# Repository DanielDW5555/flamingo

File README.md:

# Flamingo

This is the first original project I have completed from start to finish. My inspiration for this project was flamingos, and how they are usually seen balanced upright on one leg. The goal of the project was to create a self balancing robot that could stand upright for a short period of time.

The system works by interfacing the LIS3LV02DLTR accelerometer with the STM32F3 microcontroller to monitor the x and z component of acceleration. The data from the accelerometer is then used by a PID control system implemented on the microcontroller which configures the PWM duty cycle of the brushed DC motors.

The following where the requirements I used to design the robot:
  - The robot must be able to stand up right during operation
  - The robot will be powered by a 9V battery
  - All electronic devices will be implemented on a single PCB
  - The size of the PCB will be equal to or smaller than a credit card
  - No price limit on the BOM (Although my wallet will regret this later...)

The assembled robot fulfills the requirements listed above, but the PID controller requires a lot of tuning to get it to stand upright. Having a larger robot would make tuning the PID control system easier.

The following images depict the blank flamingo PCB and the rev 1 schematic.

Blank PCB

Rev 1 schematic

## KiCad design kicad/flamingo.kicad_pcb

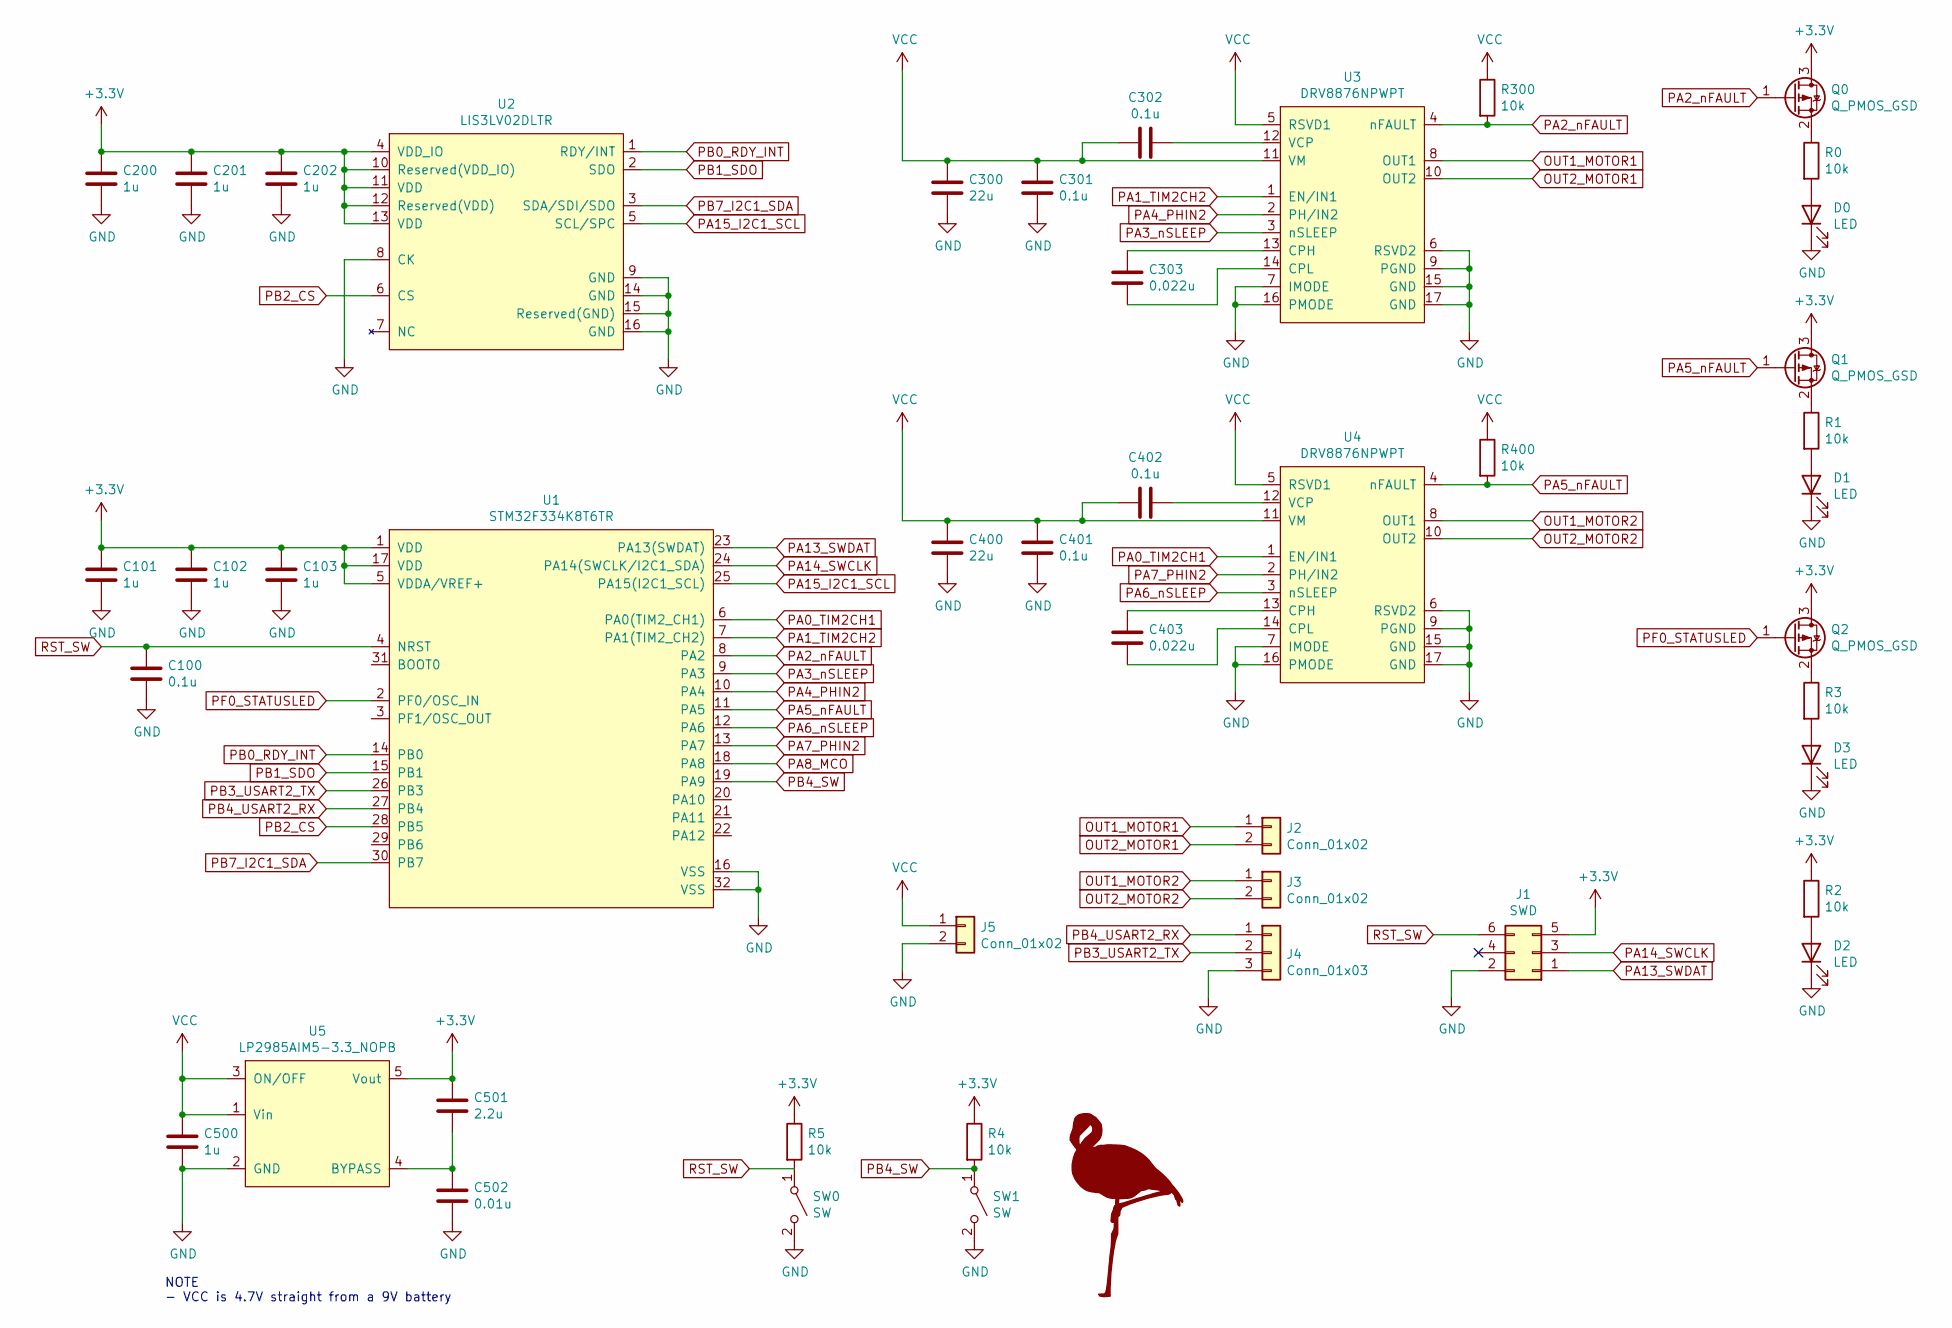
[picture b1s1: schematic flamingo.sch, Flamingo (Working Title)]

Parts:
C100, C301, C302, C401, C402: 0.1u; C_0603_1608Metric_Pad1.08x0.95mm_HandSolder; Digikey 399-C0603C104K4REC7867CT-ND
C101, C102, C103, C200, C201, C202, C500: 1u; C_0603_1608Metric_Pad1.08x0.95mm_HandSolder; Digikey 399-C0603C105K4RAC7411CT-ND
C300, C400: 22u; C_1210_3225Metric_Pad1.33x2.70mm_HandSolder; Digikey 399-1301-1-ND
C303, C403: 0.022u; C_0603_1608Metric_Pad1.08x0.95mm_HandSolder; Digikey C0603C223K3RAC7411
C501: 2.2u; C_0603_1608Metric_Pad1.08x0.95mm_HandSolder; Digikey 399-7886-1-ND
C502: 0.01u; C_0603_1608Metric_Pad1.08x0.95mm_HandSolder; Digikey 399-C0603C103M5RAC7411CT-ND
D0, D1, D2, D3: LED; LED_0603_1608Metric_Pad1.05x0.95mm_HandSolder; Digikey 754-1126-1-ND
J1: SWD; PinSocket_2x03_P1.27mm_Vertical; Digikey GRPB032VWVN-RC
J2, J3: Conn_01x02; PinHeader_1x02_P2.54mm_Vertical_SMD_Pin1Right; Digikey S1013E-02-ND
J4: Conn_01x03; PinHeader_1x03_P2.54mm_Vertical_SMD_Pin1Right; Digikey S1013EC-03-ND
J5: Conn_01x02; PinSocket_2x01_P2.54mm_Vertical_SMD; Digikey S1013E-02-ND
Q0, Q1, Q2: Q_PMOS_GSD; SOT-23; Digikey BSS84-FDICT-ND
R0, R1, R2, R3, R4, R5, R300, R400: 10k; R_0603_1608Metric_Pad0.98x0.95mm_HandSolder; Digikey RMCF0603FT10K0CT-ND
SW0, SW1: SW; SW_SPST_B3U-1000P; Digikey SW1020CT-ND
U1: STM32F334K8T6TR; LQFP-32_7x7mm_P0.8mm; Digikey 497-STM32F334K8T6TR-ND
U2: LIS3LV02DLTR; LIS3LV02DL; Digikey 497-8415-2-ND
U3, U4: DRV8876NPWPT; TSSOP-16-1EP_4.4x5mm_P0.65mm; Digikey 296-DRV8876NPWPTCT-ND
U5: LP2985AIM5-3.3_NOPB; SOT-23-5_HandSoldering; Digikey LP2985AIM5-3.3/NOPBTR-ND

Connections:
+3V3: C101.1, C102.1, C103.1, C200.1, C201.1, C202.1, C501.1, J1.5, Q0.3 (D), Q1.3 (D), Q2.3 (D), R2.1, R4.1, R5.1, U1.1 (VDD), U1.5 (VDDA/VREF+), U1.17 (VDD), U2.4 (VDD_IO), U2.10 (Reserved(VDD_IO)), U2.11 (VDD), U2.12 (Reserved(VDD)), U2.13 (VDD), U5.5 (Vout)
GND: C100.2, C101.2, C102.2, C103.2, C200.2, C201.2, C202.2, C300.2, C301.2, C400.2, C401.2, C500.2, C502.2, D0.1 (K), D1.1 (K), D2.1 (K), D3.1 (K), J1.2, J4.3, J5.2, SW0.2 (B), SW1.2 (B), U1.16 (VSS), U1.32 (VSS), U2.8 (CK), U2.9 (GND), U2.14 (GND), U2.15 (Reserved(GND)), U2.16 (GND), U3.6 (RSVD2), U3.7 (IMODE), U3.9 (PGND), U3.15 (GND), U3.16 (PMODE), U3.17 (GND), U4.6 (RSVD2), U4.7 (IMODE), U4.9 (PGND), U4.15 (GND), U4.16 (PMODE), U4.17 (GND), U5.2 (GND)
unnamed: C302.1, U3.12 (VCP)
unnamed: C303.1, U3.14 (CPL)
unnamed: C303.2, U3.13 (CPH)
unnamed: C402.2, U4.12 (VCP)
unnamed: C403.1, U4.14 (CPL)
unnamed: C403.2, U4.13 (CPH)
unnamed: C501.2, C502.1, U5.4 (BYPASS)
unnamed: D0.2 (A), R0.2
unnamed: D1.2 (A), R1.2
unnamed: D2.2 (A), R2.2
unnamed: D3.2 (A), R3.2
unnamed: Q0.2 (S), R0.1
unnamed: Q1.2 (S), R1.1
unnamed: Q2.2 (S), R3.1
OUT1_MOTOR1: J2.1, U3.8 (OUT1)
OUT1_MOTOR2: J3.1, U4.8 (OUT1)
OUT2_MOTOR1: J2.2, U3.10 (OUT2)
OUT2_MOTOR2: J3.2, U4.10 (OUT2)
PA0_TIM2CH1: U1.6 (PA0(TIM2_CH1)), U4.1 (EN/IN1)
PA1_TIM2CH2: U1.7 (PA1(TIM2_CH2)), U3.1 (EN/IN1)
PA2_nFAULT: Q0.1 (G), R300.2, U1.8 (PA2), U3.4 (nFAULT)
PA3_nSLEEP: U1.9 (PA3), U3.3 (nSLEEP)
PA4_PHIN2: U1.10 (PA4), U3.2 (PH/IN2)
PA5_nFAULT: Q1.1 (G), R400.2, U1.11 (PA5), U4.4 (nFAULT)
PA6_nSLEEP: U1.12 (PA6), U4.3 (nSLEEP)
PA7_PHIN2: U1.13 (PA7), U4.2 (PH/IN2)
PA8_MCO: U1.18 (PA8)
PA13_SWDAT: J1.1, U1.23 (PA13(SWDAT))
PA14_SWCLK: J1.3, U1.24 (PA14(SWCLK/I2C1_SDA))
PA15_I2C1_SCL: U1.25 (PA15(I2C1_SCL)), U2.5 (SCL/SPC)
PB0_RDY_INT: U1.14 (PB0), U2.1 (RDY/INT)
PB1_SDO: U1.15 (PB1), U2.2 (SDO)
PB2_CS: U1.28 (PB5), U2.6 (CS)
PB3_USART2_TX: J4.2, U1.26 (PB3)
PB4_SW: R4.2, SW1.1 (A), U1.19 (PA9)
PB4_USART2_RX: J4.1, U1.27 (PB4)
PB7_I2C1_SDA: U1.30 (PB7), U2.3 (SDA/SDI/SDO)
PF0_STATUSLED: Q2.1 (G), U1.2 (PF0/OSC_IN)
RST_SW: C100.1, J1.6, R5.2, SW0.1 (A), U1.4 (NRST)
VCC: C300.1, C301.1, C302.2, C400.1, C401.1, C402.1, C500.1, J5.1, R300.1, R400.1, U3.5 (RSVD1), U3.11 (VM), U4.5 (RSVD1), U4.11 (VM), U5.1 (Vin), U5.3 (ON/OFF)

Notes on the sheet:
NOTE - VCC is 4.7V straight from a 9V battery

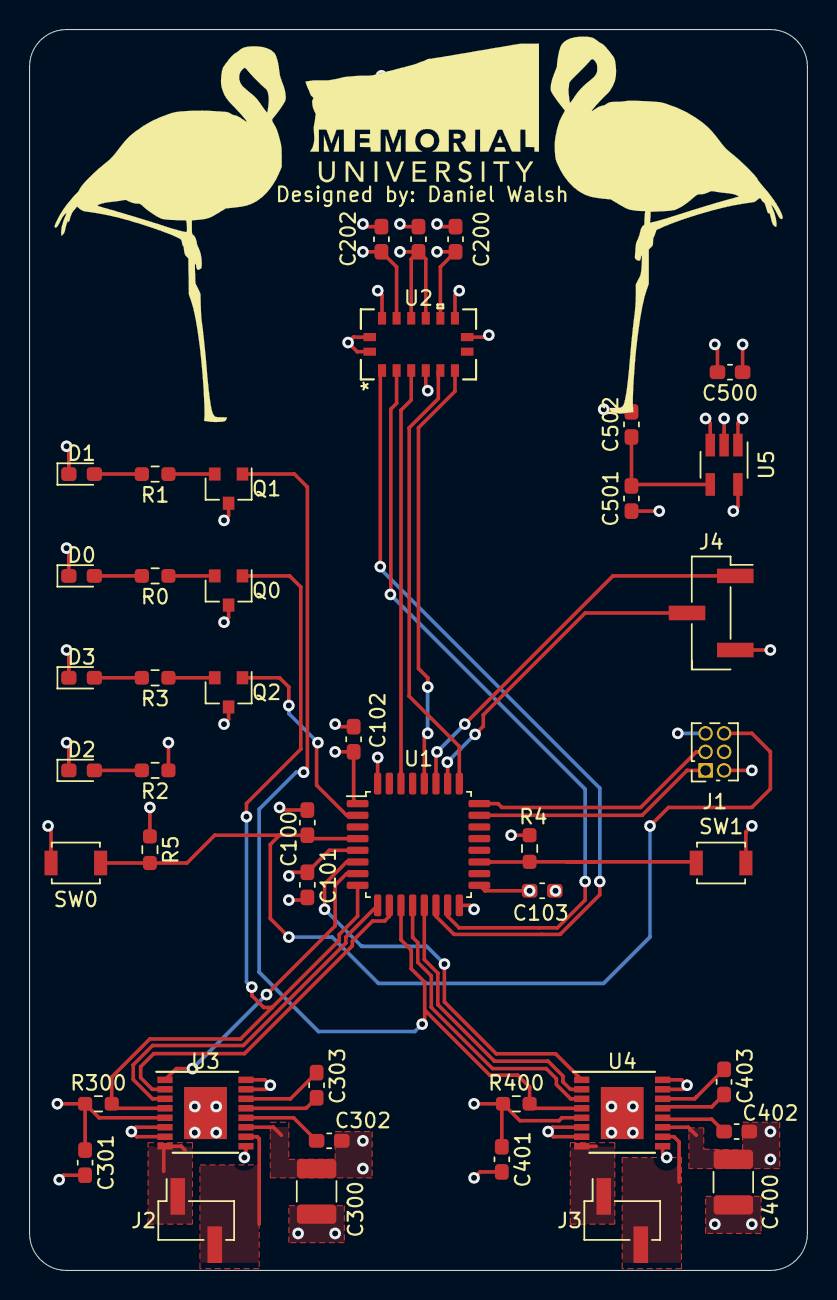
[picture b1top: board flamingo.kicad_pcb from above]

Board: 4 copper layers, 53.3 x 85.1 mm, 45 parts (1 on the bottom side), 41 nets.

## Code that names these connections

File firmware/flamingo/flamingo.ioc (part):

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Mcu.UserName=STM32F334K8Tx
RCC.HSEPLLFreq_Value=8000000
PA13.Signal=SYS_JTMS-SWDIO
PA1.Signal=S_TIM2_CH2
RCC.HSE_VALUE=8000000
PB3.Mode=Multiprocessor_communication
board=custom
PA15.Mode=I2C
PB4.Mode=Multiprocessor_communication
PF0\ /\ OSC_IN.Signal=GPIO_Output
PB7.Signal=I2C1_SDA
Mcu.Name=STM32F334K(4-6-8)Tx
PA0.Signal=S_TIM2_CH1_ETR
PB3.Signal=USART2_TX
PA4.Signal=GPIO_Output
RCC.SYSCLKFreq_VALUE=8000000
Mcu.Package=LQFP32
PB5.Signal=GPIO_Output
PA6.Signal=GPIO_Output
PB7.Mode=I2C
PA14.Signal=SYS_JTCK-SWCLK
PA15.Signal=I2C1_SCL
PB0.Signal=GPIO_Input
PB4.Signal=USART2_RX
PA3.Signal=GPIO_Output
PA7.Signal=GPIO_Output

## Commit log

2021-05-10 Init Commit
2021-05-10 Fixed README.mb images.
2021-05-10 Revision 2
    Changed the following items on the schematic and layout.
    - Disconnected SDO from U1 and U2
    - Changed U3 and U4 pull up resistors to have a source of 3.3V, not VCC
    - Added 1k I2C resistors
    - Fixed U5 BYPASS connection error
    - Updated schematic photo
2021-05-10 Updated README.mb
2021-05-10 Fixed README.mb
2021-05-10 Added goals and requirements to README.md
2021-05-10 Added goals and requirements to README.mb
2021-05-10 Changed the README.mb to display the rev 2 schematic

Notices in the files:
parts and their libraries:
Copyright 2016 Accelerated Designs. All rights reserved.
